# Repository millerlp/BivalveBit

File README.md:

# BivalveBit

A custom data logger designed to monitor bivalve mollusc heart rate, valve
gape, and external temperature. Designed to be housed in a 3/4" schedule 40 
PVC plumbing pipe along with an 18650-size Lithium-Ion battery cell. 

Current hardware revision E (Fall 2021). See the Hardware folder for KiCad
design files.

Programmed in the Arduino environment.
 
Requires the separate BivalveBit_lib library available at: 
https://github.com/millerlp/BivalveBit_lib

 Based on ATmega4808 MCU using MegaCoreX board definition
 https://github.com/MCUdude/MegaCoreX

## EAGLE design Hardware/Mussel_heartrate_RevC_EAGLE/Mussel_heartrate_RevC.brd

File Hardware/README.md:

# BivalveBit hardware
 Heart rate and valve gape sensor wearable for oysters and mussels. 
 
 * Based around a ATmega4808 microcontroller
 * Designed to fit inside a nominal 3/4" schedule 40 PVC plumbing pipe (<18.5mm
 inside diameter) along with an 18650 size Lithium-Ion battery cell. 
 * Provides one I2C 4-pin port for communicating with a IR heart rate sensor
 * Provides one analog 4-pin port for communicating with an analog sensor such
 as the A1395 Hall effect sensor (with SLEEP pin on the 4th wire). 
 * Writes data to a standard microSD card
 
 Hardware design files for the main board were originally created in KiCad 5.1, 
 in the directory BivalveBit_RevE. The files have been updated to KiCad 6.0.1. 
 
 Hardware design files for the heart rate (and temperature) sensor board
 were created in Autodesk EAGLE 9.6, and are available in the 
 Mussel_heartrate_RevC_EAGLE directory. A version imported into KiCad 6.0.1 is available
 in the directory Mussel_heartrate_RevC_KiCad. 
 
 Hardware design files in KiCad 6.0.1 for the Hall effect sensor board using an Allegro A1395
 Hall effect sensor can be found in the directory Hall_effect_sensor_board_A139x.

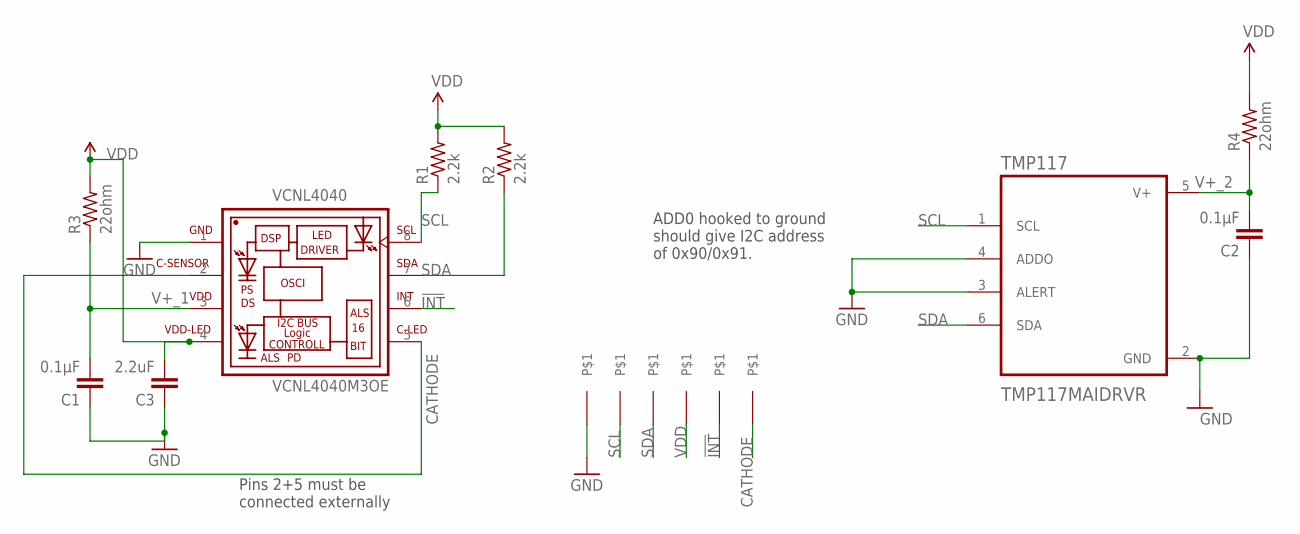
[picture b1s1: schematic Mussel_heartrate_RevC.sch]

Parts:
!INT, !INT1: PINHD-1X10.7MM_DRILL; 1X01_SMALL_0.7
C1, C2: 0.1µF; C0402
C3: 2.2uF; C0402
GND: PINHD-1X1SMALL; 1X01_SMALL
R1, R2: 2.2k; R0402
R3, R4: 22ohm; R0402
SCL: PINHD-1X1SMALL; 1X01_SMALL
SDA: PINHD-1X1SMALL; 1X01_SMALL
TMP117: TMP117MAIDRVR; SON65P200X200X80-7N
VCNL4040: VCNL4040M3OE; VISHAY_VCNL4040_4X2X1.1
VDD: PINHD-1X1SMALL; 1X01_SMALL

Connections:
!INT: !INT.P$1, VCNL4040.6 (INT)
CATHODE: !INT1.P$1, VCNL4040.2 (C-SENSOR), VCNL4040.5 (C-LED)
GND: C1.1, C2.1, C3.1, GND.1, TMP117.2 (GND), TMP117.3 (ALERT), TMP117.4 (ADDO), VCNL4040.1 (GND)
SCL: R1.1, SCL.1, TMP117.1 (SCL), VCNL4040.8 (SCL)
SDA: R2.1, SDA.1, TMP117.6 (SDA), VCNL4040.7 (SDA)
V+_1: C1.2, R3.1, VCNL4040.3 (VDD)
V+_2: C2.2, R4.1, TMP117.5 (V+)
VDD: C3.2, R1.2, R2.2, R3.2, R4.2, VCNL4040.4 (VDD-LED), VDD.1

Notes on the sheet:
ADD0 hooked to ground should give I2C address of 0x90/0x91.
Pins 2+5 must be connected externally

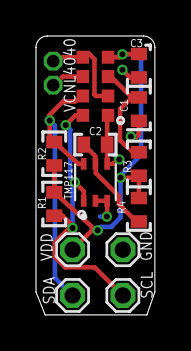
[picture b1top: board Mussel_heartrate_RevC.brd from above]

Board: 2 copper layers, 6.6 x 15.5 mm, 15 parts (0 on the bottom side), 8 nets.

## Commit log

2021-08-05 Put some info in the readme
2021-08-06 Working RTC example
    MCP79400T real time clock working
2021-08-06 adding this
2021-08-06 VCNL4040 basic test - works
2021-08-06 Tested working with 128x32 I2C display
    Purchased from Amazon: "WayinTop 3PCS 0.91 inch OLED Display Module IIC"
2021-08-06 Swap these around
2021-08-06 Tested working with RevB
    Be sure to have SdFat-beta (2.1 or later) installed
2021-08-22 Renaming test sketches
2021-08-22 Updated and working
2021-08-22 Tested working on RevB
2021-08-23 Basic working example, need to calibrate
2021-08-26 Add a link to the library
2021-08-26 Link to required libraries
2021-08-26 Basic version, several TODOs still
2021-08-27 Basic working test
2021-08-27 Renaming some files in order
2021-08-27 Sort of works with TMP117
2021-08-27 renamed
2021-08-27 Working with TMP117 sensor
2021-08-31 Renamed and removed
2021-08-31 Testing battery voltage reading
2021-09-01 Update note: Run at 8MHz, not 16MHz
2021-09-01 Fixing notes
2021-09-01 Testing different voltage references
2021-09-01 Tested working
2021-09-01 Initial setup of all peripherals
2021-09-01 Minimal working version
    For some reason some of the RevB boards were acting flaky and apparently resetting partway through the setup loop (browning out?), but in other cases they work fine.
2021-09-07 New revision
2021-09-07 Starting to add in more components
2021-09-07 Testing why the RTC doesn't start reliably
2021-09-22 Need to turn on VREG to test sensor
2021-09-22 No longer needed.
2021-09-22 Give VREG time to turn on
    Before searching for the temp sensor, make sure the VREG has powered up fully (~150 µsec)
2021-09-22 Making serial numbers, start at SN101
2021-09-22 Fix LED pin assignments, turn on VREG
2021-09-28 Building boards 103/104, with 6pF crystal caps
2021-09-29 Running at half speed on RTC?
2021-09-29 Seems to output at correct rate now
    Needed to define RTC.PER value at 32768-1 (= 32767) so that the 32.768kHz signal was causing an overflow every 32768 crystal cycles
2021-09-29 Still have a 10-tick drift on the RTC
    Maybe due to processing time?
2021-10-06 Still messing around, not great yet
2021-10-06 Moving the RTC ticks check into the GPS interrupt
2021-10-07 Fix variable type
    Need to make these signed because the RTC can run faster than GPS and result in a negative difference between the two counts.
2021-11-01 New unified test program
    Use to test newly assembled sensors
2021-11-01 Adding more messages
2021-11-01 Add 3rd digit to filename serialnumber
2021-11-01 Making new boards
2021-11-01 Fix printing sd message
2021-11-01 Testing LEDs at start
2022-01-01 Adding some comments
2022-01-01 Basic working sleep function
2022-01-01 Incomplete - working on ISR pin change
    Need to put together ISR and learn how to handle pin change interrupt correctly
2022-01-11 Working wake-from-sleep at 1Hz
2022-01-11 Nothing to see here yet
2022-01-12 Still not working
2022-01-13 Renamed and deleted
2022-01-13 Functional Periodic Interrupt Timer
2022-01-14 Testing lower powered modes
2022-01-17 Swap back to standby
2022-01-19 Working alarm pin test
2022-01-21 Starting on a main data collection version
2022-01-21 Adding 2 interrupt routines
    1 for 8Hz fast wakes, 1 for 1-minute wakeups. TODO: ensure that the 8Hz PIT disabling routine works.
    TODO: incorporate sensor sampling and SD card writing
2022-01-25 Trying to break it, still works
2022-01-25 Working test of 8Hz / 1minute timers
    Appears to swap back and forth between the 8Hz fast sampling and 1-minute interval alarms.
2022-01-26 Starting to add in more functions
    Beginning to incorporate sensor objects and getting SD card stuff going. Still need to initialize files and add code to start new files each day.
2022-01-27 Partly working - TODOs
    Need to implement the actual IR sensor reading and writing to buffer.
    Also have an issue with board going into a reset loop when on FTDI power only and no OLED screen attached, probably a voltage droop issue and lack of capacitance in the I2C bus.
2022-01-31 Using this to test settings on IR sensor
2022-01-31 TODO: fix IR sensor readout
    I'm not getting proper readout from the IR sensor right now, possibly it needs more time to awaken and integrate measurement before being read.
2022-02-01 Testing version - start battery tests
    All sensors functional, set to sample heart every other minute for 30 seconds at 8Hz.
2022-02-01 Proves that it still works
    Setting some additional parameters on the VCNL4040 and proving that it still works with rapid turn on and turn off.
2022-02-24 KiCad files
2022-02-24 Moved and renamed
2022-02-24 RevE circuit board pic
2022-02-24 Add some details
2022-02-24 Adding links and details
2022-02-28 Moving heart rate board in
2022-02-28 Explain directories
2022-03-24 Changing cutoff voltage to 3.5
2022-03-25 Changing green flash timing
    Move the green flash to only happen once a minute when the Hall effect and temperature sensor are sampled. Starting battery test at 2 minute intervals.
2022-03-30 Fix compatibility with SdFat 2.1.2
    Changed File definition to SdFile to allow this work with SdFat v2.1.2
2022-03-30 Change comments, battery cutoff voltage
2022-05-18 Adding clock setting to the main program
    You can now set the RTC in the main data logging program using the SETDATE command.
2022-05-22 Update with new picture
2022-05-30 Remove extra comma at end of each file line
    We don't need a comma after the battery voltage since it's the last value on the line.
2022-05-31 Hall effect sensor board design
2022-05-31 Heart rate module RevC in KiCad
2022-05-31 Updating hardware file commentary
2022-05-31 Updated to KiCad 6.0.1
2022-11-21 Init commit - need to rewrite this
2022-12-01 Filenaming not working yet
    Fix the initFileName function so it stops borking the year.
2022-12-02 Try this with a working board next
2022-12-02 Fixed file naming - test hardware next
2022-12-02 Return to idle after clock setting
2022-12-02 Add some comments
2022-12-02 Increase pause
2022-12-02 Increase the wait time
    Syringe pump would miss triggers if the wait time between trigger events was less than 1500 milliseconds.
2022-12-06 Notes
2023-01-05 Updated heart sensor to 200MA & 8T
2023-01-27 Images of layout
2023-05-12 Let user know VCNL4040 was found
2023-07-03 Creating code to use MAX3010x heart sensor - UNTESTED
2023-07-06 Functional test for MAX30102 - but use 5V supply
2023-07-06 Faster sampling
2023-07-10 Making this a bit more user-friendly, fail gracefully
    Should be functional for testing if the various sensors (gape sensor, VCNL4040, TMP117) and clock/SD are all functional.
2024-05-20 ignore
